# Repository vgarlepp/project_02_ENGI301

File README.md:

# Project 2, ENGI 301, Vanessa Garlepp
This project aims to create an example schematic and layout for an Etch-A-Sketch device. The folder also contains manufacturing files, a bill of materials, and a mechanical block diagram in the form of a Powerpoint. Further pictures of documentation are in the "docs" folder, and EAGLE files are within the EAGLE folder.

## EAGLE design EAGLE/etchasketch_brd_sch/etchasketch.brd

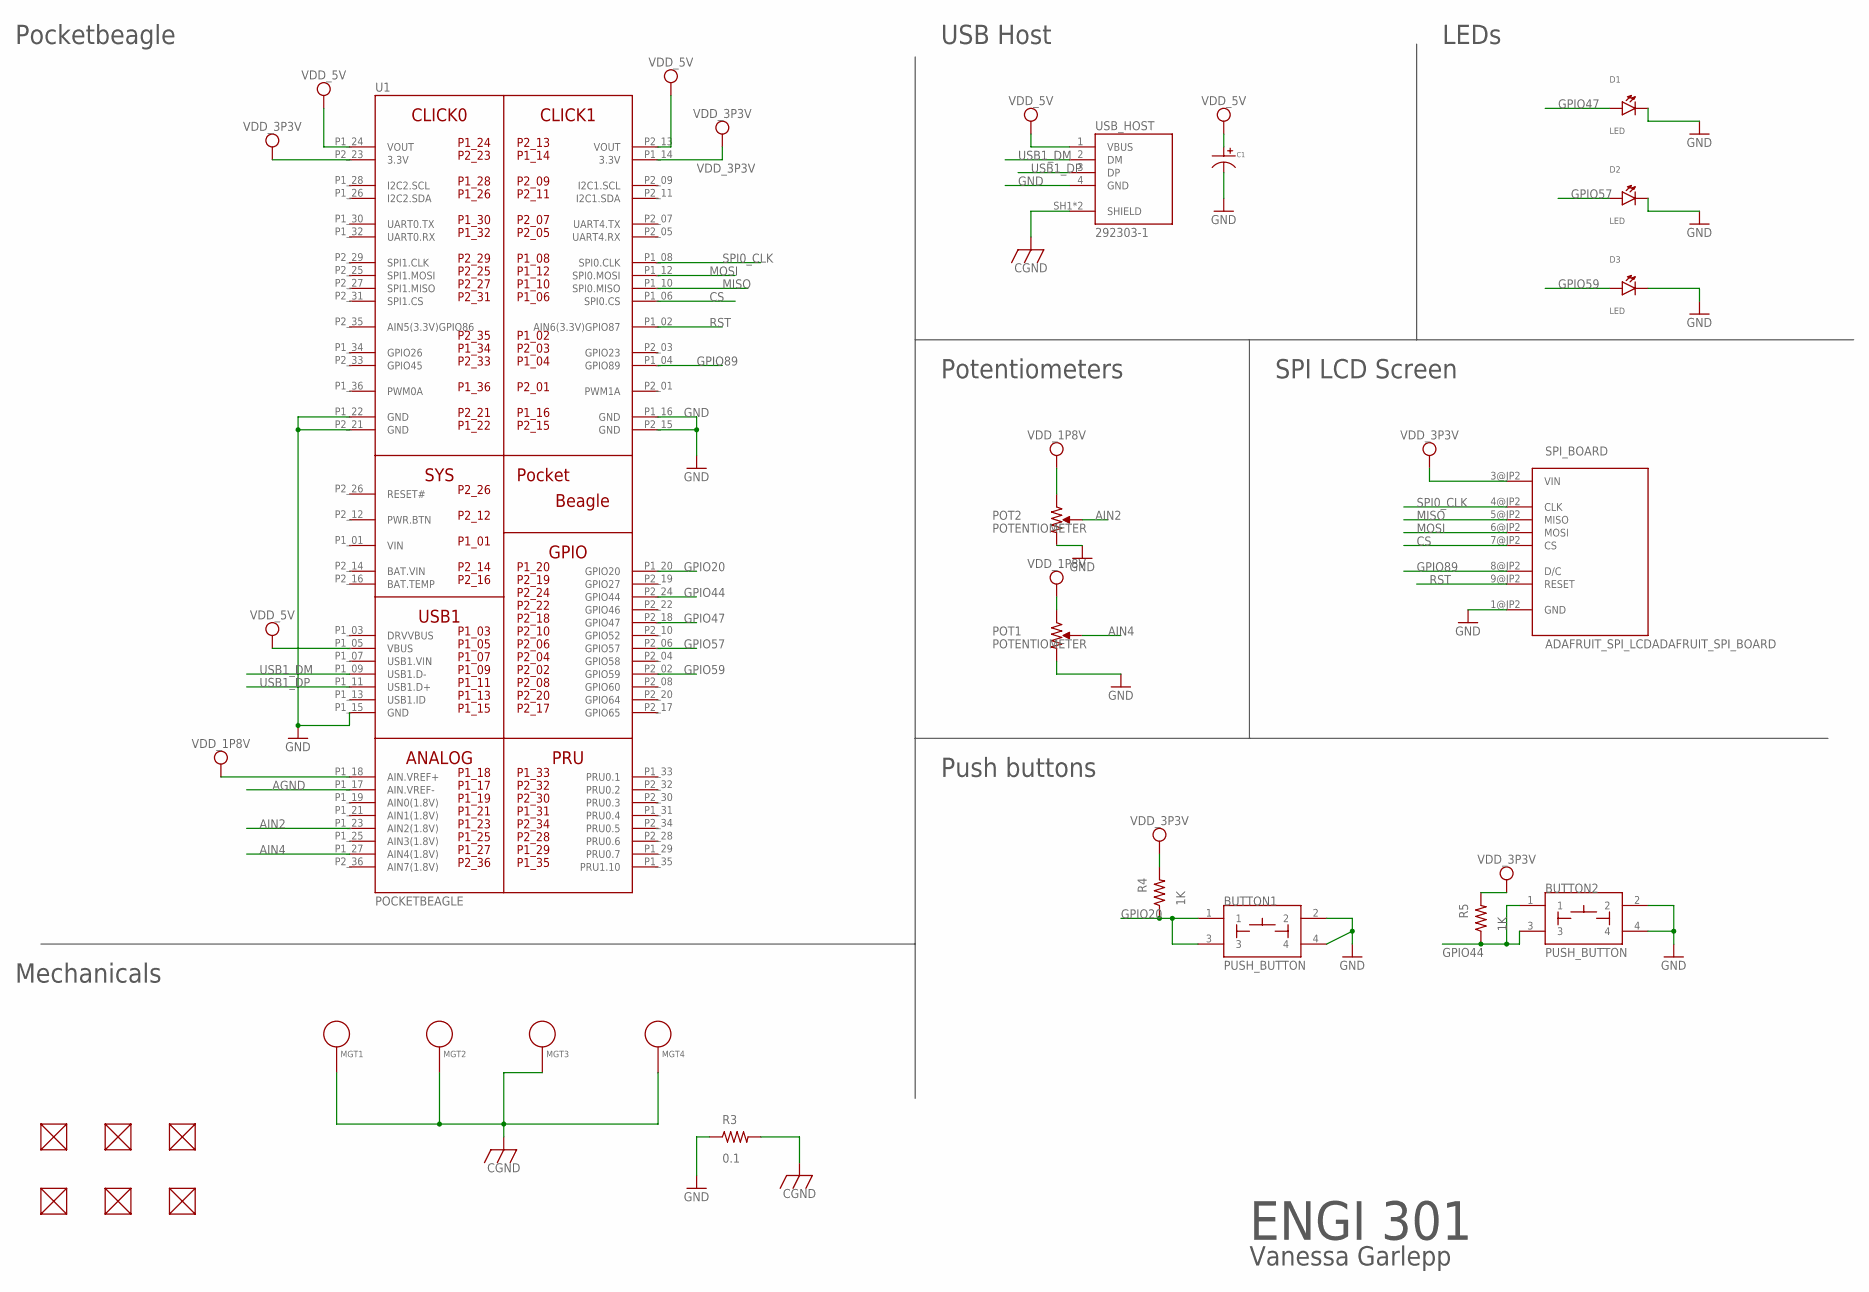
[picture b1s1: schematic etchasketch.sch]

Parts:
BUTTON1, BUTTON2: PUSH_BUTTON; BUTTON_12.5MM
C1: CAPACITOR_P_10MM; CP10MM
D1, D2, D3: LED; EIA-STD
FUD1, FUD2, FUD3, FUD4, FUD5, FUD6: FIDUCIAL; FIDUCIAL_40MIL
MGT1, MGT2, MGT3, MGT4: MOUNTING_HOLE
POT1, POT2: POTENTIOMETER; POT-PO90S
R3: 0.1; R0603
R4, R5: 1K; R0402
SPI_BOARD: ADAFRUIT_SPI_LCDADAFRUIT_SPI_BOARD; ADAFRUIT_SPI_BOARD
U1: POCKETBEAGLE
USB_HOST: 292303-1; TE_292303-1

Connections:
AGND: U1.P1_17 (AIN.VREF-)
AIN2: POT2.S, U1.P1_23 (AIN2(1.8V))
AIN4: POT1.S, U1.P1_27 (AIN4(1.8V))
BAT.VIN: U1.P2_14 (BAT.VIN)
CGND: MGT1.P$1, MGT2.P$1, MGT3.P$1, MGT4.P$1, R3.2, USB_HOST.SH1 (SHIELD), USB_HOST.SH2 (SHIELD)
CS: SPI_BOARD.7@JP2 (CS), U1.P1_06 (SPI0.CS)
GND: BUTTON1.2, BUTTON1.4, BUTTON2.2, BUTTON2.4, C1.P$2, D1.CATHODE, D2.CATHODE, D3.CATHODE, POT1.CW, POT2.CW, R3.1, SPI_BOARD.1@JP2 (GND), U1.P1_15 (GND), U1.P1_16 (GND), U1.P1_22 (GND), U1.P2_15 (GND), U1.P2_21 (GND), USB_HOST.4 (GND)
GPIO20: BUTTON1.1, BUTTON1.3, R4.1, U1.P1_20 (GPIO20)
GPIO44: BUTTON2.1, BUTTON2.3, R5.1, U1.P2_24 (GPIO44)
GPIO47: D1.ANODE, U1.P2_18 (GPIO47)
GPIO57: D2.ANODE, U1.P2_06 (GPIO57)
GPIO59: D3.ANODE, U1.P2_02 (GPIO59)
GPIO89: SPI_BOARD.8@JP2 (D/C), U1.P1_04 (GPIO89)
MISO: SPI_BOARD.5@JP2 (MISO), U1.P1_10 (SPI0.MISO)
MOSI: SPI_BOARD.6@JP2 (MOSI), U1.P1_12 (SPI0.MOSI)
RST: SPI_BOARD.9@JP2 (RESET), U1.P1_02 (AIN6(3.3V)GPIO87)
SPI0_CLK: SPI_BOARD.4@JP2 (CLK), U1.P1_08 (SPI0.CLK)
USB1_DM: U1.P1_09 (USB1.D-), USB_HOST.2 (DM)
USB1_DP: U1.P1_11 (USB1.D+), USB_HOST.3 (DP)
VDD_1P8V: POT1.CCW, POT2.CCW, U1.P1_18 (AIN.VREF+)
VDD_3P3V: R4.2, R5.2, SPI_BOARD.3@JP2 (VIN), U1.P1_14 (3.3V), U1.P2_23 (3.3V)
VDD_5V: C1.P$1, U1.P1_05 (VBUS), U1.P1_24 (VOUT), U1.P2_13 (VOUT), USB_HOST.1 (VBUS)
VIN: U1.P1_01 (VIN)

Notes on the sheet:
Pocketbeagle
USB Host
Potentiometers
SPI LCD Screen
LEDs
Push buttons
Mechanicals
ENGI 301
Vanessa Garlepp

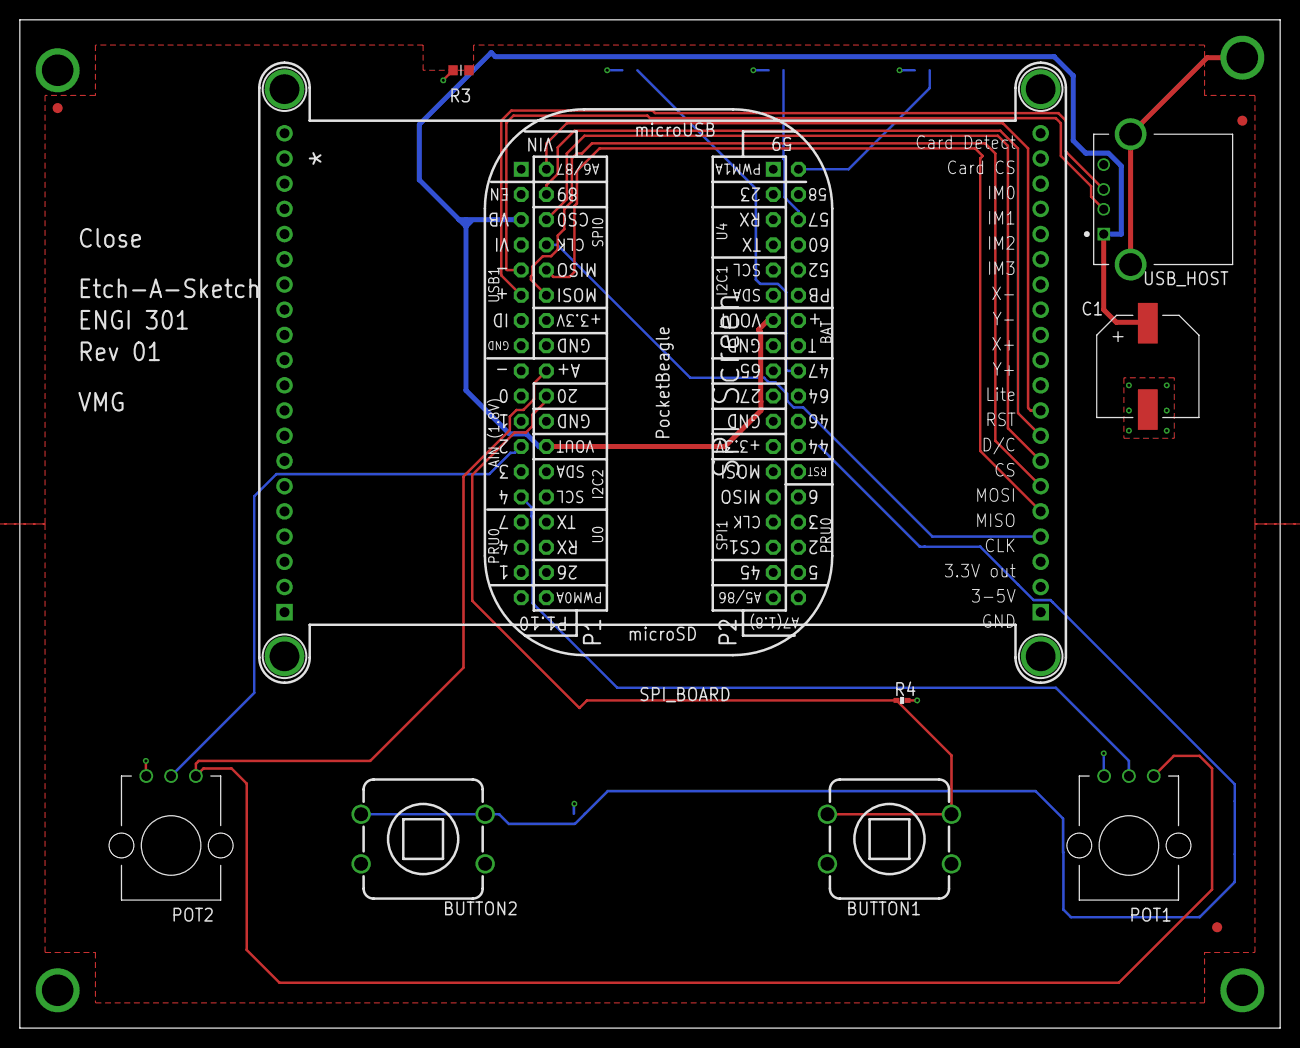
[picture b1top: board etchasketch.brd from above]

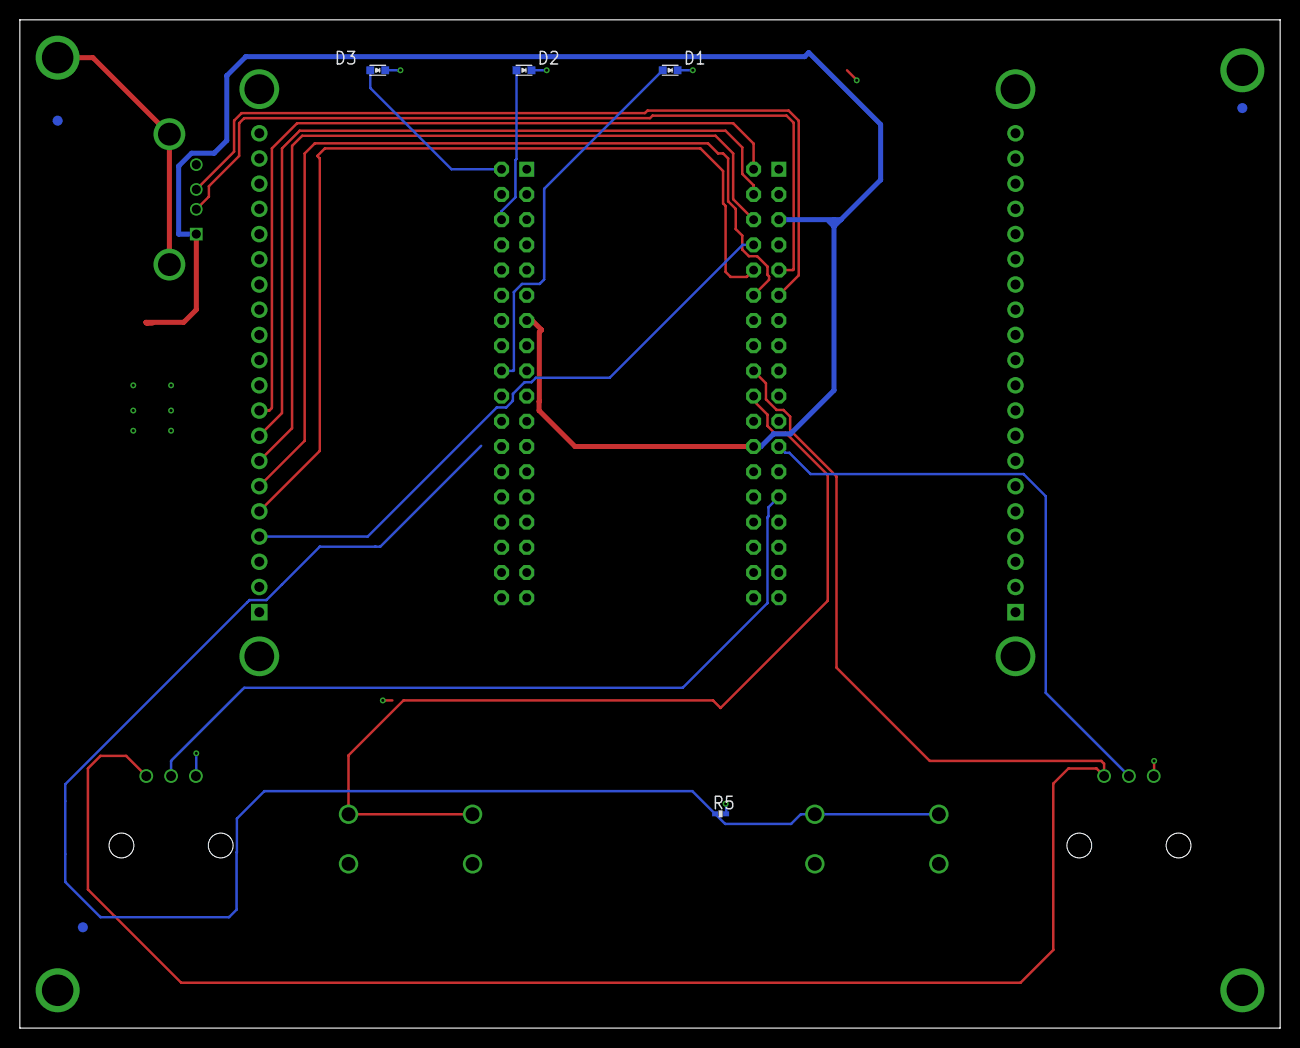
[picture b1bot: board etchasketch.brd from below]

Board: 4 copper layers, 127.0 x 101.6 mm, 24 parts (7 on the bottom side), 20 nets.

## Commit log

2022-12-03 ENGI301_project_02_Garlepp
2022-12-03 Changed project folders
2022-12-06 added DS store
2022-12-09 All new files for etch-a-sketch creation
2022-12-09 deleted pcb folder
2022-12-09 Edited files
2022-12-09 ppt edits
2022-12-09 new ppt
